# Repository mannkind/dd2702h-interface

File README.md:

# Home Automation - DD2702H

A **quick and dirty** interface to the DD2702H remote.

Seriously. This is hacky hack hacky. But it's all hidden in a nice little case, so I don't really care.  
It requires removing the DD2702H from the stock case, soldering some wires to it, and hooking up an esp32.

## Build of Materials

* 1 - DD2702H remote
* 1 - Custom PCB
* 1 - Nekmit Dual Port Ultra Thin Flat USB Wall Charger
* 1 - Wemos D1 Mini (esp32)
* 2 - Strips of female connectors for Wemos D1 Mini
* 3 - 1k through-hole resistors
* 3 - 2N3904 PNP transistors
* 1 - DD2702H Remote
* 11 - Male pins; angled preferred
* Some wires to connect them

## Program

The [example yaml](program/dd2702h.yaml) for ESPHome contains all you should need to get started. 
ESPHome is awesome, and I'm lazy.

## PCB

I ordered the PCB from OSHPark.com by uploading the KiCAD files.
Turn-around time was a week, and the boards from OSHPark are high quality.

## Case 

The case I've printed and am using is provided in the `case` folder as an `.stl` file. 
There's also the openscad source, if you're interested. It requires [YAPP_Box](https://github.com/mrWheel/YAPP_Box) to work.

**Assembly Guide**

* Remove remote PCB from stock enclosure
* Solder wires to the up/stop/down buttons; optionally the channel buttons (I skipped the channel buttons)
* Solder ground wire to remote button battery holder
* Solder female pins into Wemos D1 Mini spot
* Solder resistors
* Solder transistors matching silkscreen
* Solder male header pins
* Solder wires to remote buttons as desired - one end should be a female connector
* Use electrical tape to hold the battery in position
* Use electrical tape to protect the bottom of the custom PCB
* Insert the remote PCB into the case; it should fit nicely on the pegs
* Place a dab of hotglue in the center; place the custom PCB on top of it
* Connect a USB cable to the Nekmit; hot glue that sucker down
* Put the lid on the case
* Plug into wall

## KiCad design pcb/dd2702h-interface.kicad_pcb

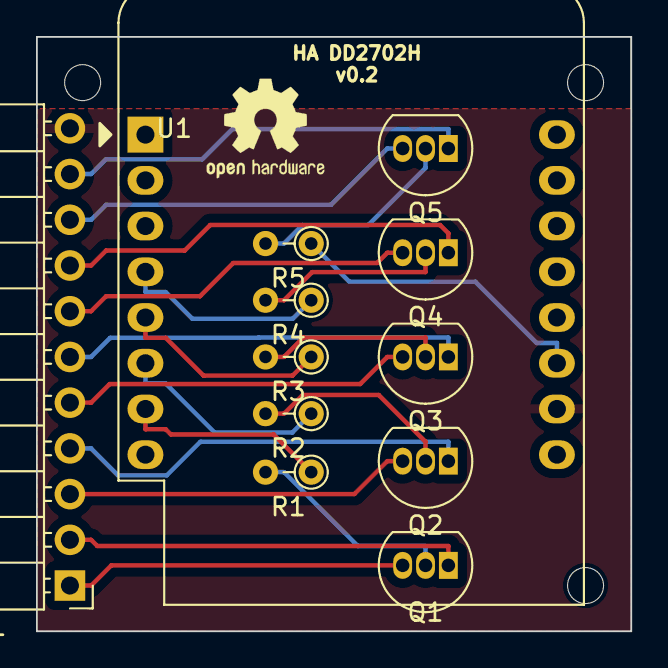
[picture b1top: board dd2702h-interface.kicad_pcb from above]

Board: 2 copper layers, 33.0 x 33.0 mm, 12 parts (0 on the bottom side), 21 nets.

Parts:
J1: Conn_01x11_Pin; PinHeader_1x11_P2.54mm_Horizontal
Q1, Q2, Q3, Q4, Q5: 2N3904; TO-92_Inline
R1, R2, R3, R4, R5: R_US; R_Axial_DIN0204_L3.6mm_D1.6mm_P2.54mm_Vertical
U1: WeMos_D1_mini; WEMOS_D1_mini_light

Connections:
CH_DOWN_C: J1.7, Q4.3 (C)
CH_DOWN_E: J1.8, Q4.1 (E)
CH_UP_C: J1.9, Q5.3 (C)
CH_UP_E: J1.10, Q5.1 (E)
DOWN_C: J1.5, Q3.3 (C)
DOWN_E: J1.6, Q3.1 (E)
GND: J1.11, U1.10 (GND)
GPIO2: R5.1, U1.11 (D4)
GPIO12: R3.1, U1.5 (MISO/D6)
GPIO13: R2.1, U1.6 (MOSI/D7)
GPIO14: R4.1, U1.4 (SCK/D5)
GPIO15: R1.1, U1.7 (CS/D8)
unnamed: Q1.2 (B), R1.2
unnamed: Q2.2 (B), R2.2
unnamed: Q3.2 (B), R3.2
unnamed: Q4.2 (B), R4.2
unnamed: Q5.2 (B), R5.2
STOP_C: J1.3, Q2.3 (C)
STOP_E: J1.4, Q2.1 (E)
UP_C: J1.1, Q1.3 (C)
UP_E: J1.2, Q1.1 (E)

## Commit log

2023-08-05 Mounting holes; autorouted
2023-08-05 Add the case w/pcb rendered
